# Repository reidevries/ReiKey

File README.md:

# ReiKey

This is a 101-key plateless PCB-based mechanical keyboard inspired by [JayK](https://github.com/josuegaleas/JayK) and [ONO-SENDAI MATRIX 83](https://imgur.com/a/v5pzh#FiXKcm0) as well as the Amiga 500 keyboard layout.

## Layout:
I went in the opposite route of most modern mechanical keyboards and used larger-size keys without any layers or "function" key. It is organised roughly into four sections - the numpad on the left, the alphanumeric keys in the middle, and navigation keys on the right, with a function key row on the top.

The numpad is on the left to improve ergonomics for data entry. The mouse is a kind of navigation function, so with the mouse on the right, the navigation keys and mouse are clustered together instead of having a numpad between them. In an IBM style layout, I would have to swap hands a lot to switch between the arrow keys and mouse while entering data with the numpad.

The top row and navigation keys are all 1.5U - inspired by the Amiga 500 keyboard which has larger function and delete keys. They are a bit easier to hit as a result. The escape key being on the far right might seem strange, but I really prefer it after using it for a while. The placement of insert and escape keys is really excellent for use with Vim keybindings - I can use insert to enter insert mode and the escape key right next to it to get back to normal mode. I removed the scroll lock and pause/break keys because I have never used them in my life. I removed the printscreen key because it seems superfluous to have a special key for such a specific function, instead I have a keycombo to capture screenshots in my window manager.

The alphanumeric keys are mostly similar to an IBM keyboard, however I opted for the "bigass" enter key because it just feels so good to hit. Instead of a tiny backspace key, I have a regular-size backspace. I rearranged the grave and backslash keys to make room, shrinking the capslock key which I almost never use. Inspired by Unix and Amiga keyboards, the whole left modifier section is extended. This means both shift keys are a full 2.75U. The 2U tab is great for programming where tab is used very regularly.
 
There is an extra key to the left of the left arrow key, which I am using to open an application launcher. You could also map it as a function key if you want some of the missing keys or media controls or something.
 
## Hardware Design:
The PCB is intended to be sandwiched between two pieces of wood, a top one with a cutout in the middle for all the keys, and a bottom one with a cutout for the Teensy LC. If a harder material than wood is used, you might need to make space for the pins of the switches and the SMD resistors. Softer materials don't have this requirement because the switch pins can stab into them a bit without issue. Eight M3 screws hold the pieces together. I chose a plateless design for simplicity and to reduce parts count.

## Electronic Design:
It uses a Teensy LC as the microcontroller. I chose this because it is very small and low cost.
It has a 10x10 keyboard matrix with the delete key going directly to ground. The only LEDs are under the caps lock and num lock keys, and a power LED above the arrow keys. I would recommend using 470 ohm resistors for the caps and num lock LEDs and a higher value resistor like 1.5k ohm for the power LED as the power LED is constantly on and can get annoying if it's too bright.

## Finding keycaps:
I succesfully built this keyboard and have been using it as my daily driver for several months now. The most difficult part was finding keycaps for the unusual layout. First, I ordered a full DSA keycap set which had a "bigass" enter key included; it was quite difficult to find this type of enter key in DSA. Then I ordered about 24 blank 1.5U keys in colours that complemented the initial keycap set, and 4 blank 2.75U keys for the dual 2.75U shifts. Then for the Tab and Command keys, I ordered some custom-printed individual DSA keycaps from signature plastics for 5 dollars each. I was easily able to find a key with an LED hole for the numlock key, but I still haven't found one suitable for the 1.25U capslock. I would highly recommend using DSA keycaps as it has the same profile for every row, unlike all other key profiles like DCS, OEM, SA etc. 

If you want to custom-design a keycap set to fit this keyboard, you will need to include at least:
* "bigass" enter key
* 2U Tab
* 1.25U caps lock, preferrably with some way for the LED to shine through it.
* Dual 2.75U shift keys
* Dual 1.5U control keys
* One 1.5U command key and one 1.25U command key

It's relatively easy to find 1.5U blanks so I'd consider them less important to include as they will add a lot of cost to a regular keycap set. But if you want, the required 1.5U keys include F1 to F12, Delete, Insert, Escape, Page Up, Page Down, Home, and End

## PCB:
The PCB is made in Kicad and requires [keebs.pretty](https://github.com/egladman/keebs.pretty) for the keyboard footprints. I had to make a custom footprint for the ""bigass"" enter key.
It also requires the teensy [symbol](https://github.com/XenGi/teensy_library) and [footprint](https://github.com/XenGi/teensy.pretty) libraries from github user XenGi.
The PCB still has an older layout written on the silkscreen.

## Programming:
I used C with the Teensy/Arduino keyboard libraries to register keypresses and send them to a computer. Thanks to @cruxic for the [Teensy makefile](https://github.com/cruxic/teensy-makefile). It has a delay of ~150us between checking each column to avoid duplicate keypresses. Simply build the board, plug in the Teensy LC via usb, install Teensy/arduino libraries correctly, then type `make load` and you should get a working keyboard. NOTE: You may need to edit the ROWS or COLS in main.c to get the layout working for your keyboard. I burnt some pins on my teensy and remapped.

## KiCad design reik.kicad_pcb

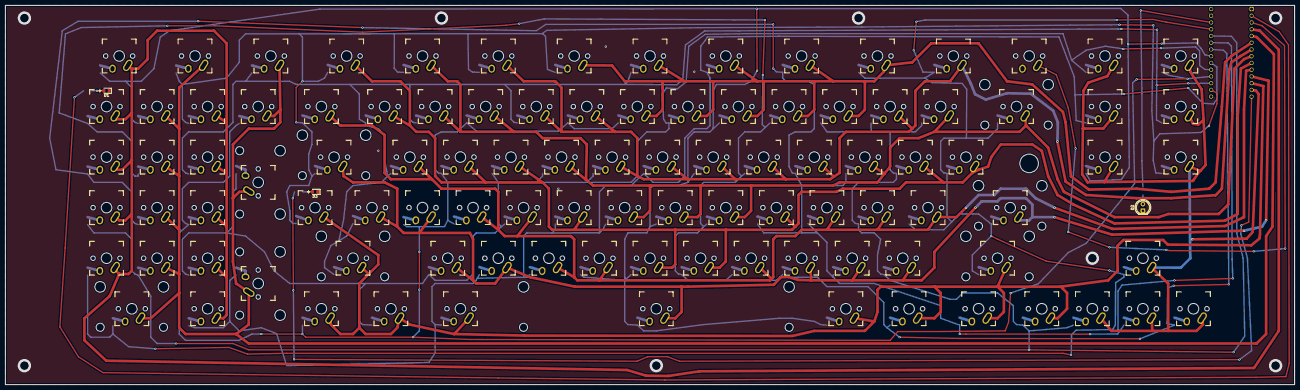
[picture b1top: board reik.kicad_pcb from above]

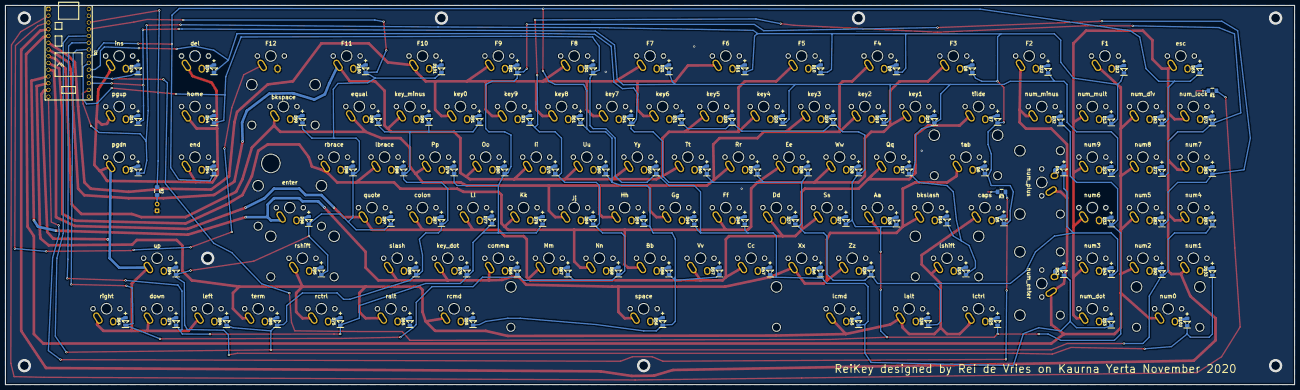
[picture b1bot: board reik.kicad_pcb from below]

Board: 2 copper layers, 485.8 x 142.9 mm, 208 parts (104 on the bottom side), 128 nets.

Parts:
D1: num_led; LED0805_handsolder
D2: pwr_led; LED_D5.0mm
D3: caps_led; LED0805_handsolder
D4, D5, D6, D7, D8, D9, D10, D11, D12, D13, D14, D15, D16, D17, D18, D19, D20, D21, D22, D23, D24, D25, D26, D27, D28, D29, D30, D31, D32, D33, D34, D35, D36, D37, D38, D39, D40, D41, D42, D43, D44, D45, D46, D47, D48, D49, D50, D51, D52, D53, D54, D55, D56, D57, D58, D59, D60, D61, D62, D63, D64, D65, D66, D67, D68, D69, D70, D71, D72, D73, D74, D75, D76, D77, D78, D79, D80, D81, D82, D83, D84, D85, D86, D87, D88, D89, D90, D91, D92, D93, D94, D95, D96, D97, D98, D99, D100, D101, D102, D103: D_Small_ALT; D1206
R1, R3: 330; R_1206_3216Metric_Pad1.42x1.75mm_HandSolder
R2: 1k; R_1206_3216Metric_Pad1.42x1.75mm_HandSolder
SW1: pgdn; Mx_Alps_150
SW2: caps; Mx_Alps_125
SW3: tab; Mx_Alps_200
SW4: tilde; Mx_Alps_150
SW5: F3; Mx_Alps_150
SW6: F4; Mx_Alps_150
SW7: F5; Mx_Alps_150
SW8: F6; Mx_Alps_150
SW9: F1; Mx_Alps_150
SW10: num_mult; Mx_Alps_100
SW11: F12; Mx_Alps_150
SW12: pgup; Mx_Alps_150
SW13: lshift; Mx_Alps_275
SW14: bkslash; Mx_Alps_100
SW15: Qq; Mx_Alps_100
SW16: key1; Mx_Alps_100
SW17: key2; Mx_Alps_100
SW18: key4; Mx_Alps_100
SW19: F7; Mx_Alps_150
SW20: F2; Mx_Alps_150
SW21: num9; Mx_Alps_100
SW22: ins; Mx_Alps_150
SW23: lctrl; Mx_Alps_150
SW24: Aa; Mx_Alps_100
SW25: Ss; Mx_Alps_100
SW26: Ww; Mx_Alps_100
SW27: key3; Mx_Alps_100
SW28: key5; Mx_Alps_100
SW29: key6; Mx_Alps_100
SW30: num_minus; Mx_Alps_100
SW31: num6; Mx_Alps_100
SW32: del; Mx_Alps_150
SW33: lalt; Mx_Alps_125
SW34: Zz; Mx_Alps_100
SW35: Dd; Mx_Alps_100
SW36: Ee; Mx_Alps_100
SW37: Rr; Mx_Alps_100
SW38: Tt; Mx_Alps_100
SW39: key7; Mx_Alps_100
SW40: num_plus; Mx_Alps_200
SW41: num3; Mx_Alps_100
SW42: home; Mx_Alps_150
SW43: lcmd; Mx_Alps_150
SW44: Xx; Mx_Alps_100
SW45: Cc; Mx_Alps_100
SW46: Ff; Mx_Alps_100
SW47: Gg; Mx_Alps_100
SW48: Yy; Mx_Alps_100
SW49: F8; Mx_Alps_150
SW50: num_enter; Mx_Alps_200
SW51: num_dot; Mx_Alps_100
SW52: end; Mx_Alps_150
SW53: rcmd; Mx_Alps_125
SW54: space; Mx_Alps_625
SW55: Vv; Mx_Alps_100
SW56: Bb; Mx_Alps_100
SW57: Hh; Mx_Alps_100
SW58: Uu; Mx_Alps_100
SW59: key8; Mx_Alps_100
SW60: num_div; Mx_Alps_100
SW61: esc; Mx_Alps_150
SW62: right; Mx_Alps_100
SW63: ralt; Mx_Alps_125
SW64: comma; Mx_Alps_100
SW65: Mm; Mx_Alps_100
SW66: Nn; Mx_Alps_100
SW67: Jj; Mx_Alps_100
SW68: Ii; Mx_Alps_100
SW69: key9; Mx_Alps_100
SW70: num8; Mx_Alps_100
SW71: num_lock; Mx_Alps_100
SW72: down; Mx_Alps_100
SW73: rctrl; Mx_Alps_150
SW74: key_dot; Mx_Alps_100
SW75: Ll; Mx_Alps_100
SW76: Kk; Mx_Alps_100
SW77: Pp; Mx_Alps_100
SW78: Oo; Mx_Alps_100
SW79: F9; Mx_Alps_150
SW80: num5; Mx_Alps_100
SW81: num7; Mx_Alps_100
SW82: left; Mx_Alps_100
SW83: term; Mx_Alps_100
SW84: slash; Mx_Alps_100
SW85: colon; Mx_Alps_100
SW86: lbrace; Mx_Alps_100
SW87: equal; Mx_Alps_100
SW88: key_minus; Mx_Alps_100
SW89: key0; Mx_Alps_100
SW90: num2; Mx_Alps_100
SW91: num4; Mx_Alps_100
SW92: up; Mx_Alps_100
SW93: rshift; Mx_Alps_275
SW94: enter; Mx_Alps_BigEnter
SW95: quote; Mx_Alps_100
SW96: rbrace; Mx_Alps_100
SW97: bkspace; Mx_Alps_200
SW98: F11; Mx_Alps_150
SW99: F10; Mx_Alps_150
SW100: num0; Mx_Alps_200
SW101: num1; Mx_Alps_100
U1: Teensy-LC; TeensyLC_outer

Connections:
/Matrix/col01: D4.1, D5.1, D6.1, D7.1, D8.1, D9.1, D10.1, D11.1, D12.1, D13.1, U1.21
/Matrix/col02: D14.1, D15.1, D16.1, D17.1, D18.1, D19.1, D20.1, D21.1, D22.1, D23.1, U1.22
/Matrix/col03: D24.1, D25.1, D26.1, D27.1, D28.1, D29.1, D30.1, D31.1, D32.1, D33.1, U1.23
/Matrix/col04: D34.1, D35.1, D36.1, D37.1, D38.1, D39.1, D40.1, D41.1, D42.1, D43.1, U1.24
/Matrix/col05: D44.1, D45.1, D46.1, D47.1, D48.1, D49.1, D50.1, D51.1, D52.1, D53.1, U1.25
/Matrix/col06: D54.1, D55.1, D56.1, D57.1, D58.1, D59.1, D60.1, D61.1, D62.1, D63.1, U1.26
/Matrix/col07: D64.1, D65.1, D66.1, D67.1, D68.1, D69.1, D70.1, D71.1, D72.1, D73.1, U1.27
/Matrix/col08: D74.1, D75.1, D76.1, D77.1, D78.1, D79.1, D80.1, D81.1, D82.1, D83.1, U1.28
/Matrix/col09: D84.1, D85.1, D86.1, D87.1, D88.1, D89.1, D90.1, D91.1, D92.1, D93.1, U1.29
/Matrix/col10: D94.1, D95.1, D96.1, D97.1, D98.1, D99.1, D100.1, D101.1, D102.1, D103.1, U1.30
/Matrix/row01: SW1.1, SW12.1, SW22.1, SW32.1, SW42.1, SW52.1, SW62.1, SW72.1, SW82.1, SW92.1, U1.13
/Matrix/row02: SW2.1, SW13.1, SW23.1, SW33.1, SW43.1, SW53.1, SW63.1, SW73.1, SW83.1, SW93.1, U1.12
/Matrix/row03: SW3.1, SW14.1, SW24.1, SW34.1, SW44.1, SW54.1, SW64.1, SW74.1, SW84.1, SW94.1, U1.11
/Matrix/row04: SW4.1, SW15.1, SW25.1, SW35.1, SW45.1, SW55.1, SW65.1, SW75.1, SW85.1, SW95.1, U1.10
/Matrix/row05: SW5.1, SW16.1, SW26.1, SW36.1, SW46.1, SW56.1, SW66.1, SW76.1, SW86.1, SW96.1, U1.9
/Matrix/row06: SW6.1, SW17.1, SW27.1, SW37.1, SW47.1, SW57.1, SW67.1, SW77.1, SW87.1, SW97.1, U1.8
/Matrix/row07: SW7.1, SW18.1, SW28.1, SW38.1, SW48.1, SW58.1, SW68.1, SW78.1, SW88.1, SW98.1, U1.7
/Matrix/row08: SW8.1, SW19.1, SW29.1, SW39.1, SW49.1, SW59.1, SW69.1, SW79.1, SW89.1, SW99.1, U1.6
/Matrix/row09: SW9.1, SW20.1, SW30.1, SW40.1, SW50.1, SW60.1, SW70.1, SW80.1, SW90.1, SW100.1, U1.5
/Matrix/row10: SW10.1, SW21.1, SW31.1, SW41.1, SW51.1, SW61.1, SW71.1, SW81.1, SW91.1, SW101.1, U1.4
/Matrix/row11: SW11.1, U1.3
GND: D1.1, D2.1, D3.1, SW11.2, U1.1, U1.32
unnamed: D1.2, R1.2
unnamed: D2.2, R2.2
unnamed: D3.2, R3.2
unnamed: D4.2, SW1.2
unnamed: D5.2, SW2.2
unnamed: D6.2, SW3.2
unnamed: D7.2, SW4.2
unnamed: D8.2, SW5.2
unnamed: D9.2, SW6.2
unnamed: D10.2, SW7.2
unnamed: D11.2, SW8.2
unnamed: D12.2, SW9.2
unnamed: D13.2, SW10.2
unnamed: D14.2, SW12.2
unnamed: D15.2, SW13.2
unnamed: D16.2, SW14.2
unnamed: D17.2, SW15.2
unnamed: D18.2, SW16.2
unnamed: D19.2, SW17.2
unnamed: D20.2, SW18.2
unnamed: D21.2, SW19.2
unnamed: D22.2, SW20.2
unnamed: D23.2, SW21.2
unnamed: D24.2, SW22.2
unnamed: D25.2, SW23.2
unnamed: D26.2, SW24.2
unnamed: D27.2, SW25.2
unnamed: D28.2, SW26.2
unnamed: D29.2, SW27.2
unnamed: D30.2, SW28.2
unnamed: D31.2, SW29.2
unnamed: D32.2, SW30.2
unnamed: D33.2, SW31.2
unnamed: D34.2, SW32.2
unnamed: D35.2, SW33.2
unnamed: D36.2, SW34.2
unnamed: D37.2, SW35.2
unnamed: D38.2, SW36.2
unnamed: D39.2, SW37.2
unnamed: D40.2, SW38.2
unnamed: D41.2, SW39.2
unnamed: D42.2, SW40.2
unnamed: D43.2, SW41.2
unnamed: D44.2, SW42.2
unnamed: D45.2, SW43.2
unnamed: D46.2, SW44.2
unnamed: D47.2, SW45.2
unnamed: D48.2, SW46.2
unnamed: D49.2, SW47.2
unnamed: D50.2, SW48.2
unnamed: D51.2, SW49.2
unnamed: D52.2, SW50.2
unnamed: D53.2, SW51.2
unnamed: D54.2, SW52.2
unnamed: D55.2, SW53.2
unnamed: D56.2, SW54.2
unnamed: D57.2, SW55.2
unnamed: D58.2, SW56.2
unnamed: D59.2, SW57.2
unnamed: D60.2, SW58.2
unnamed: D61.2, SW59.2
unnamed: D62.2, SW60.2
unnamed: D63.2, SW61.2
unnamed: D64.2, SW62.2
unnamed: D65.2, SW63.2
unnamed: D66.2, SW64.2
unnamed: D67.2, SW65.2
unnamed: D68.2, SW66.2
unnamed: D69.2, SW67.2
unnamed: D70.2, SW68.2
unnamed: D71.2, SW69.2
unnamed: D72.2, SW70.2
unnamed: D73.2, SW71.2
unnamed: D74.2, SW72.2
unnamed: D75.2, SW73.2
unnamed: D76.2, SW74.2
unnamed: D77.2, SW75.2
unnamed: D78.2, SW76.2
unnamed: D79.2, SW77.2
unnamed: D80.2, SW78.2
unnamed: D81.2, SW79.2
unnamed: D82.2, SW80.2
unnamed: D83.2, SW81.2
unnamed: D84.2, SW82.2
unnamed: D85.2, SW83.2
unnamed: D86.2, SW84.2
unnamed: D87.2, SW85.2
unnamed: D88.2, SW86.2
unnamed: D89.2, SW87.2
unnamed: D90.2, SW88.2
unnamed: D91.2, SW89.2
unnamed: D92.2, SW90.2
unnamed: D93.2, SW91.2
unnamed: D94.2, SW92.2
unnamed: D95.2, SW93.2
unnamed: D96.2, SW94.2
unnamed: D97.2, SW95.2
unnamed: D98.2, SW96.2
unnamed: D99.2, SW97.2
unnamed: D100.2, SW98.2
unnamed: D101.2, SW99.2
unnamed: D102.2, SW100.2
unnamed: D103.2, SW101.2
unnamed: R1.1, U1.2
unnamed: R2.1, U1.31
unnamed: R3.1, U1.14

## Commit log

2020-12-10 add hardware files
2020-12-10 remove hardware files from wrong place in file structure
2020-12-10 add keyboard image
2020-12-10 add software folder
2021-02-06 update to new keyboard mapping
2021-02-21 update image, add kle json, update layout and readme
2021-02-21 fix dot points
2021-02-21 fix dot points again
2021-03-17 put pin assignment in separate file for portability
2021-03-17 optimize by making function args const
2021-03-17 convert some if checks to switch statements
